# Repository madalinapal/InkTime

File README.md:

# InkTime Smartwatch

## Overview
InkTime Watch is a low-power smartwatch based on the nRF52840 microcontroller, designed for efficient timekeeping, motion tracking, and e-paper display usage.

## Hardware diagram & features

This is an open-hardware wearable based on the nRF52840 microcontroller. It is fully compatible with embedded C/C++ development and comes with the following features:

* [nRF52840](https://files.seeedstudio.com/wiki/XIAO-BLE/Nano_BLE_MCU-nRF52840_PS_v1.1.pdf) microcontroller (ARM Cortex-M4F @ 64 MHz, Bluetooth 5 / BLE, 2.4 GHz radio, 1 MB Flash and 256 KB RAM, multiple interfaces: SPI, I2C, UART, GPIO, support for external antenna)
* [E-paper Display](https://www.waveshare.com/1.54inch-e-paper-module.htm?srsltid=AfmBOooLaZDBFF5ey5FPMcwvfQjNszGLTJooliuUE0Pt89mi3RbbW3zz) 1.54 inch, 200x200 resolution, communicating via SPI interface
* [BMA423](https://watchy.sqfmi.com/assets/files/BST-BMA423-DS000-1509600-950150f51058597a6234dd3eaafbb1f0.pdf) accelerometer (3-axis ultra-low-power MEMS accelerometer, integrated step counting and activity recognition, motion detection interrupts, FIFO buffer, I2C/SPI interface, optimized for wearable low-power applications)
* [BQ25180](https://www.ti.com/product/BQ25180) LiPo Charger (I2C-controlled single-cell Li-Ion/Li-Po charger, 5V USB input, up to ~250 mA charging current, integrated power path management, ultra-low power for wearables)
* [250 mAh LiPo battery](https://elektronik.ropla.eu/pdf/stock/aky/aky1119.pdf)
* [FIT0774](https://www.tme.eu/ro/details/df-fit0774/motoare-dc/dfrobot/fit0774/) vibration motor (small DC vibration motor, 10 mm diameter, 2.7 mm height, 1.5–4.2 V operating voltage, used for haptic feedback in wearable devices)
* [TC2030-IDC](https://www.digikey.ro/ro/products/detail/tag-connect-llc/TC2030-IDC/4571121) debug connector (Tag-Connect 10-pin SWD programming interface, no-socket pogo-pin connector, supports SWDIO, SWDCLK, RESET, VCC and GND, used for low-profile in-circuit debugging of MCUs)
* [DRV2605L](https://www.ti.com/product/DRV2605L) haptic driver (I2C-controlled vibration motor driver with integrated haptic library, supports ERM and LRA actuators, automatic resonance tuning, low-power operation for wearable haptic feedback systems)
* [DS6160A](https://www.mouser.com/datasheet/2/1458/DS6160A_02-3104604.pdf?srsltid=AfmBOorjUBAXZpq5Z5uEI1jLcgjTr8TjWB5ry58Sj_L0fmmZSXPHWXP2) regulator (dual-channel low-power audio power amplifier / driver IC, designed for small speaker or actuator applications, wide supply voltage range, high efficiency Class-D operation, suitable for compact battery-powered systems)
* [MAX17048](https://www.analog.com/en/products/max17048.html) fuel gauge (ultra-low-power single-cell Li-ion battery fuel gauge IC, I2C interface, uses ModelGauge algorithm for accurate state-of-charge estimation, no external sense resistor required, optimized for wearable and portable devices)

## Bill of Materials (BOM)

The table below summarizes the main components used in the project. Passive components are grouped by type and package to improve readability.

| Component | Description | Qty | Manufacturer | Part Number | Datasheet | 
|----------|------------|-----|--------------|-------------|-----------|
| nRF52840 | BLE Microcontroller | 1 | Nordic Semiconductor | nRF52840 | [Datasheet](https://files.seeedstudio.com/wiki/XIAO-BLE/Nano_BLE_MCU-nRF52840_PS_v1.1.pdf) | 
| BMA423 | 3-axis accelerometer (IMU) | 1 | Bosch | BMA423 | [Datasheet](https://watchy.sqfmi.com/assets/files/BST-BMA423-DS000-1509600-950150f51058597a6234dd3eaafbb1f0.pdf) |
| BQ25180 | Battery charger / PMIC | 1 | Texas Instruments | BQ25180 | [Datasheet](https://www.ti.com/product/BQ25180) |
| DRV2605L | Haptic driver | 1 | Texas Instruments | DRV2605L | [Datasheet](https://www.ti.com/product/DRV2605L) |
| MAX17048 | Fuel gauge | 1 | Analog Devices | MAX17048G+T10 | [Datasheet](https://www.analog.com/en/products/max17048.html) | 
| RT6160 | Buck-boost converter | 1 | Richtek | RT6160AWSC | [Datasheet](https://www.mouser.com/datasheet/2/1458/DS6160A_02-3104604.pdf) | 
| 2450AT18B100E | 2.4GHz chip antenna | 1 | Johanson Technology | 2450AT18B100E | [Datasheet](https://jlcpcb.com/api/file/downloadByFileSystemAccessId/8588940948130156544) |
| TC2030-IDC | Programming connector | 1 | Tag-Connect | TC2030-IDC | [Datasheet](https://www.lcsc.com/datasheet/C5444772.pdf) | 
| USB-C Connector | Power & data interface | 1 | Kinghelm | KH-TYPE-C-16P | [Datasheet](https://jlcpcb.com/api/file/downloadByFileSystemAccessId/8588905154556923904) | 
| FPC Connector | E-paper display connector | 1 | Molex | 503480-2400 |[Datasheet](https://www.molex.com/content/dam/molex/molexdotcom/products/automated/enus/salesdrawingpdf/503/503480/5034802400_sd.pdf?inline)| 
| Push Buttons | Tactile switches | 3 | Panasonic | EVP-AKE31A | [Datasheet](https://wmsc.lcsc.com/wmsc/upload/file/pdf/v2/lcsc/2301111010_PANASONIC-EVPAKE31A_C569760.pdf) | 
| MOSFETs | Power switching | 2 | Vishay / Diodes Inc. | SI1308EDL / DMG2305UX | [Datasheet](https://www.lcsc.com/datasheet/C469327.pdf) | 
| Diodes | Schottky diodes | 3 | ON Semiconductor | MBR0530 | [Datasheet](https://www.lcsc.com/datasheet/C77336.pdf) | 
| ESD Protection | USB protection | 1 | STMicroelectronics | USBLC6-2SC6 | [Datasheet](https://www.lcsc.com/datasheet/C7519.pdf) | 
| Crystal | 32MHz | 1 | NDK | NX2016SA-32MHZ-EXS00A-CS11336 | [Datasheet](https://wmsc.lcsc.com/wmsc/upload/file/pdf/v2/lcsc/2312080231_NDK-NX2016SA-32MHZ-EXS00A-CS11336_C6134317.pdf) | 
| Crystals | 32.768kHz | 1 | Seiko Epson | FC-135 32.7680KA-A3 | [Datasheet](https://jlcpcb.com/partdetail/SeikoEpson-FC_135_32_7680KAA3/C2650472) | 

## nRF52840 Pin Mapping

| Pin nRF52840 | Signal      | Component | Interface |
|-------------|------------|------------|----------|
| P0.00/XL1   | XL1        | Crystal X2 (32.768kHz) | XTAL |
| P0.01/XL2   | XL2        | Crystal X2 (32.768kHz) | XTAL |
| P0.05/AIN3  | EPD_CS     | E-Paper (J1 FPC) | SPI CS |
| P0.06       | SDA        | BMA423, BQ25180, MAX17048, DRV2605 | I2C SDA |
| P0.07       | SCL        | BMA423, BQ25180, MAX17048, DRV2605 | I2C SCL |
| P0.08       | IMU_INT1   | BMA423 | GPIO Input |
| P1.08       | IMU_INT2   | BMA423 | GPIO Input |
| P0.11       | PMIC_INT   | BQ25180 | GPIO Input |
| P0.12       | HAPTIC_EN  | DRV2605 | GPIO |
| VBUS        | VBUS       | USB-C (J4) | Power |
| D-          | D-         | USB-C (J4) / USBLC6 | USB |
| D+          | D+         | USB-C (J4) / USBLC6 | USB |
| P0.13       | SW_UP      | Buton Up | GPIO Input |
| P0.14       | SW_ENT     | Buton Enter | GPIO Input |
| P0.15       | EPD_DC     | E-Paper (J1 FPC) | SPI DC |
| P0.16       | EPD_RST    | E-Paper (J1 FPC) | GPIO |
| P0.17       | EPD_BUSY   | E-Paper (J1 FPC) | GPIO Input |
| P0.18/RESET | RESET      | TC2030-IDC | SWD/GPIO |
| SWDCLK      | SWDCLK     | TC2030-IDC | SWD |
| SWDIO       | SWDIO      | TC2030-IDC | SWD |
| P1.02       | SW_DN      | Buton Down | GPIO Input |
| P0.10/NFC2  | ALERT      | MAX17048 | GPIO Input |
| ANT         | RF         | Antena 2450AT18B100E | RF |
| P0.02/AIN0  | SCK        | E-Paper (J1 FPC) | SPI SCK |
| P0.03/AIN1  | MOSI       | E-Paper (J1 FPC) | SPI MOSI |

## Design Log

This section describes the PCB design process, decisions taken during implementation, and how the project complies with the imposed design constraints.

---

###  Placement Strategy

The layout process started with the placement of mechanically constrained and critical components such as:
- USB-C connector
- Side buttons
- E-paper display connector (FPC)
- nRF52840 microcontroller

These components were positioned according to the mechanical enclosure to ensure proper alignment and usability.

All components were placed exclusively on the **TOP layer**, as required. Passive components (resistors, capacitors) were then distributed around their corresponding ICs, minimizing trace length and ensuring proper decoupling.

Special attention was given to **100nF decoupling capacitors**, which were placed as close as possible to the power pins of each integrated circuit.

---

###  Routing Strategy

Routing was performed on a **4-layer PCB stack-up**, structured as follows:
- Top Layer – signal routing and component placement
- Inner Layer 1 – solid ground plane (GND)
- Inner Layer 2 – power plane (VCC, 3V3, etc.)
- Bottom Layer – signal routing

The routing process followed a hierarchical approach:
- Power traces (VCC, VBUS, 3V3) were routed first
- Signal traces were routed afterwards

Design rules applied:
- Power traces: **≥ 0.3 mm width** 
- Signal traces: **≥ 0.15 mm width**
- No 90° angles were used (only smooth or 45° routing)

The use of internal planes significantly improved power distribution and return paths, reducing noise and ensuring signal integrity.

---

###  Grounding and Planes

A solid grounding strategy was implemented using **polygon pours** on ground layers.

- Ground planes were applied on multiple layers
- **Via stitching** was used extensively to connect ground planes
- Increased via density was applied near the RF section

This improves:
- Signal return paths
- Noise reduction
- EMI performance

---

###  RF and Antenna Considerations

The antenna area was treated as a strict keep-out zone:
- No copper
- No traces
- No vias

---

### Component Constraints

All components respect the required footprint rules:

- Resistors: **0201**
- Capacitors ≤100nF: **0201**
- Capacitors >100nF: **0402**
  
## Design Rule Exceptions (Accepted)

**Trace Width (accepted):**  
Power nets (3V3, VREG, VBAT, VBUS) follow the 0.3 mm rule, but in dense areas around the nRF52840 and tightly packed components, traces are locally reduced due to limited space. These segments are short and were accepted after verification.

**Copper Clearance (accepted):**  
The minimum clearance rule (0.15 mm) is slightly violated in congested regions, especially near the nRF52840 and 0201 components. All cases were manually checked to ensure no shorts.

**Board Edge Clearance (accepted):**  
The USB-C connector (J4) and buttons (SW_UP, SW_DN, SW_ENT) extend beyond the PCB edge for enclosure alignment. This is intentional.

This ensures high-density integration suit

## Repository contens
- schematic.sch → Schematic design file  
- board.brd → PCB layout file  

### Manufacturing
- GerberFiles.zip → PCB manufacturing files (Gerber + drill files)  
- bom.csv / bom.xlsx → Bill of Materials  
- pick&place.cpl → Component placement file 

### Mechanical
- smartwatch_exploded_view.stp → Full 3D exploded view (PCB + battery + display + enclosure)  
- smartwatch.stp → Full 3D view 

### Images
- pcb_2d.png 
- pcb_3d_top_view.png
- pcb_3d_bottom_view.png
- pcb_3d_side_view
- block_diagram.jpg
- smartwatch_final.png
- smartwatch_side_view1.png
- smartwatch_side_view2.png
- smartwatch_exploded_view.png

### License
- LICENSE → Open-source license file 

### Documentation
- README.md → Main project documentation

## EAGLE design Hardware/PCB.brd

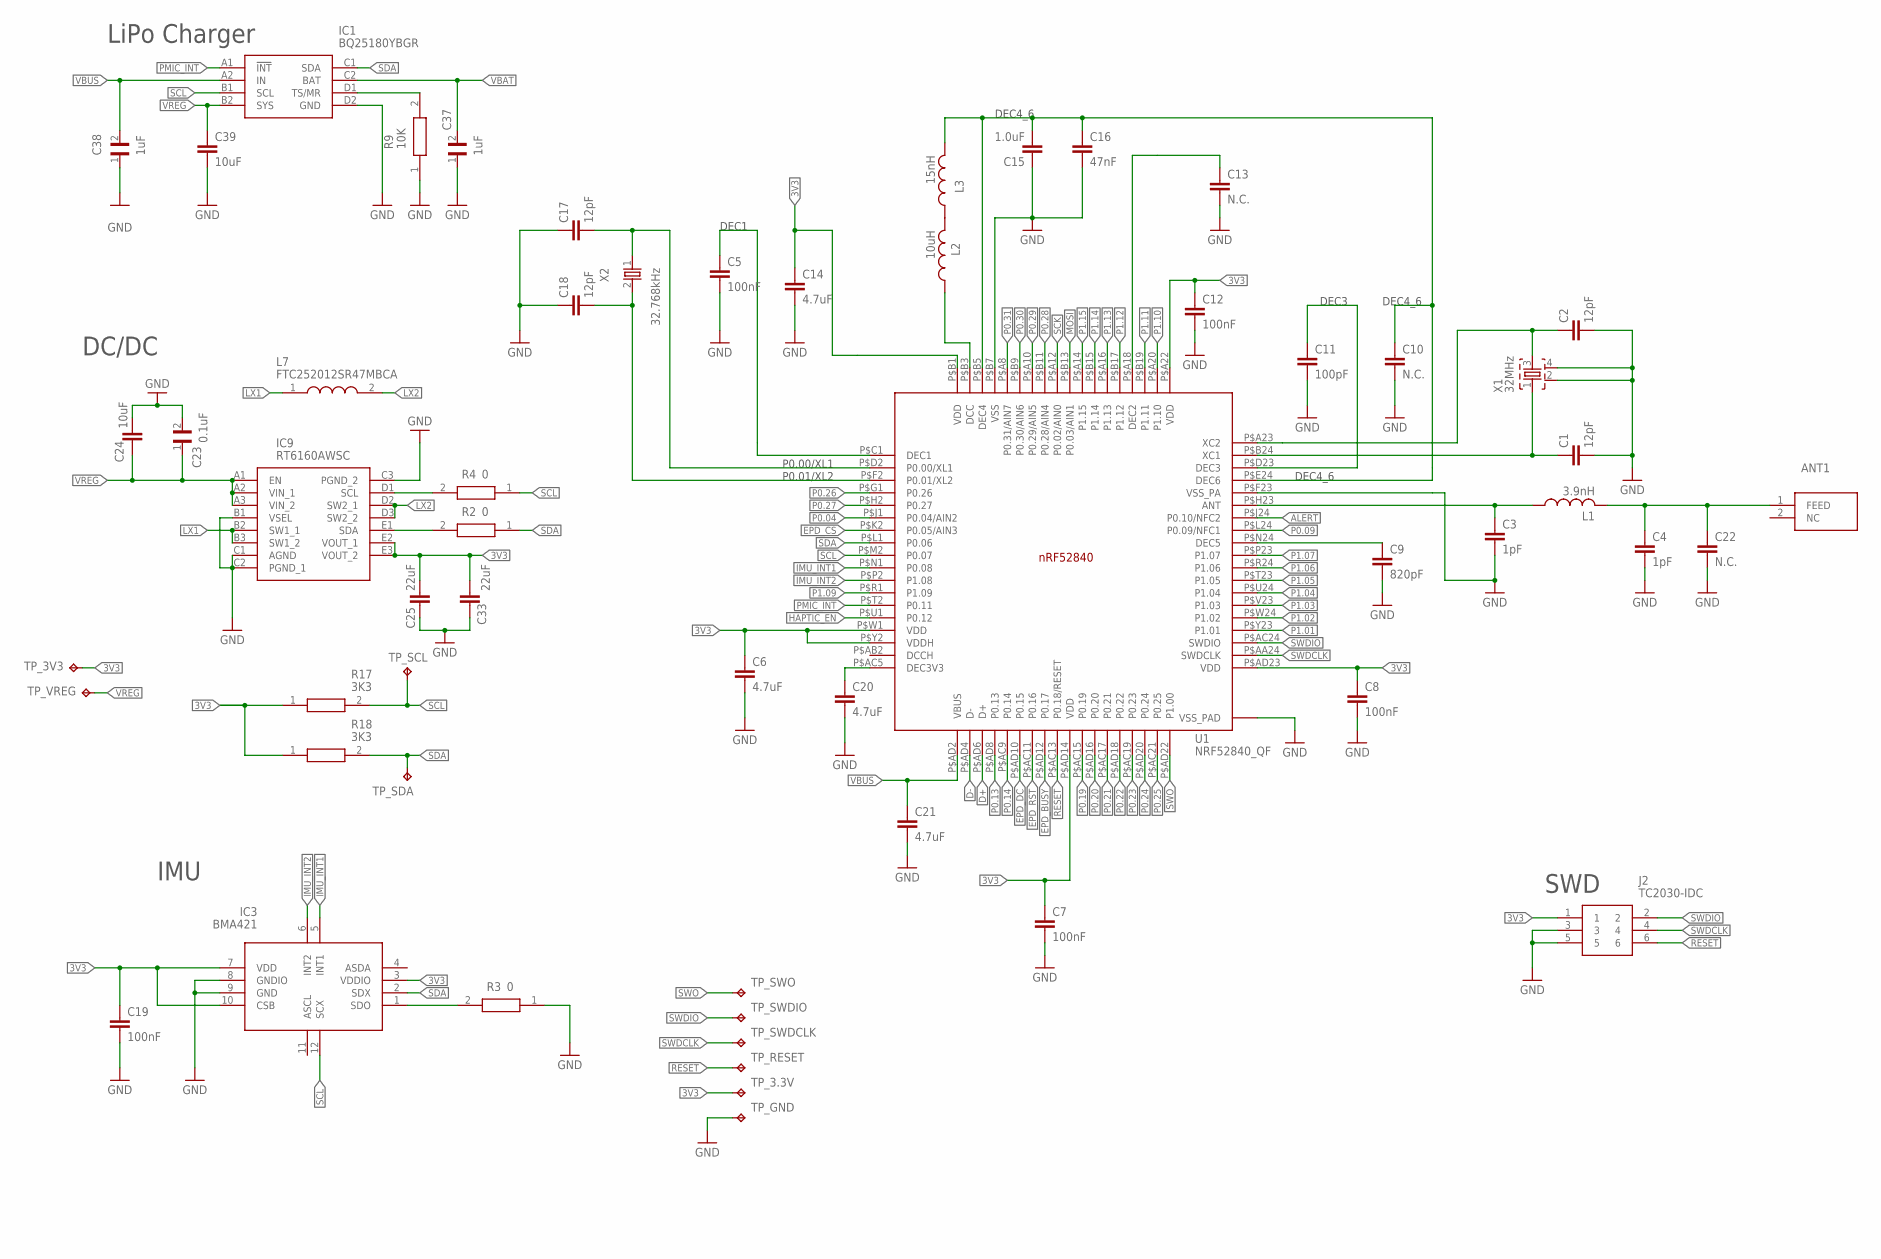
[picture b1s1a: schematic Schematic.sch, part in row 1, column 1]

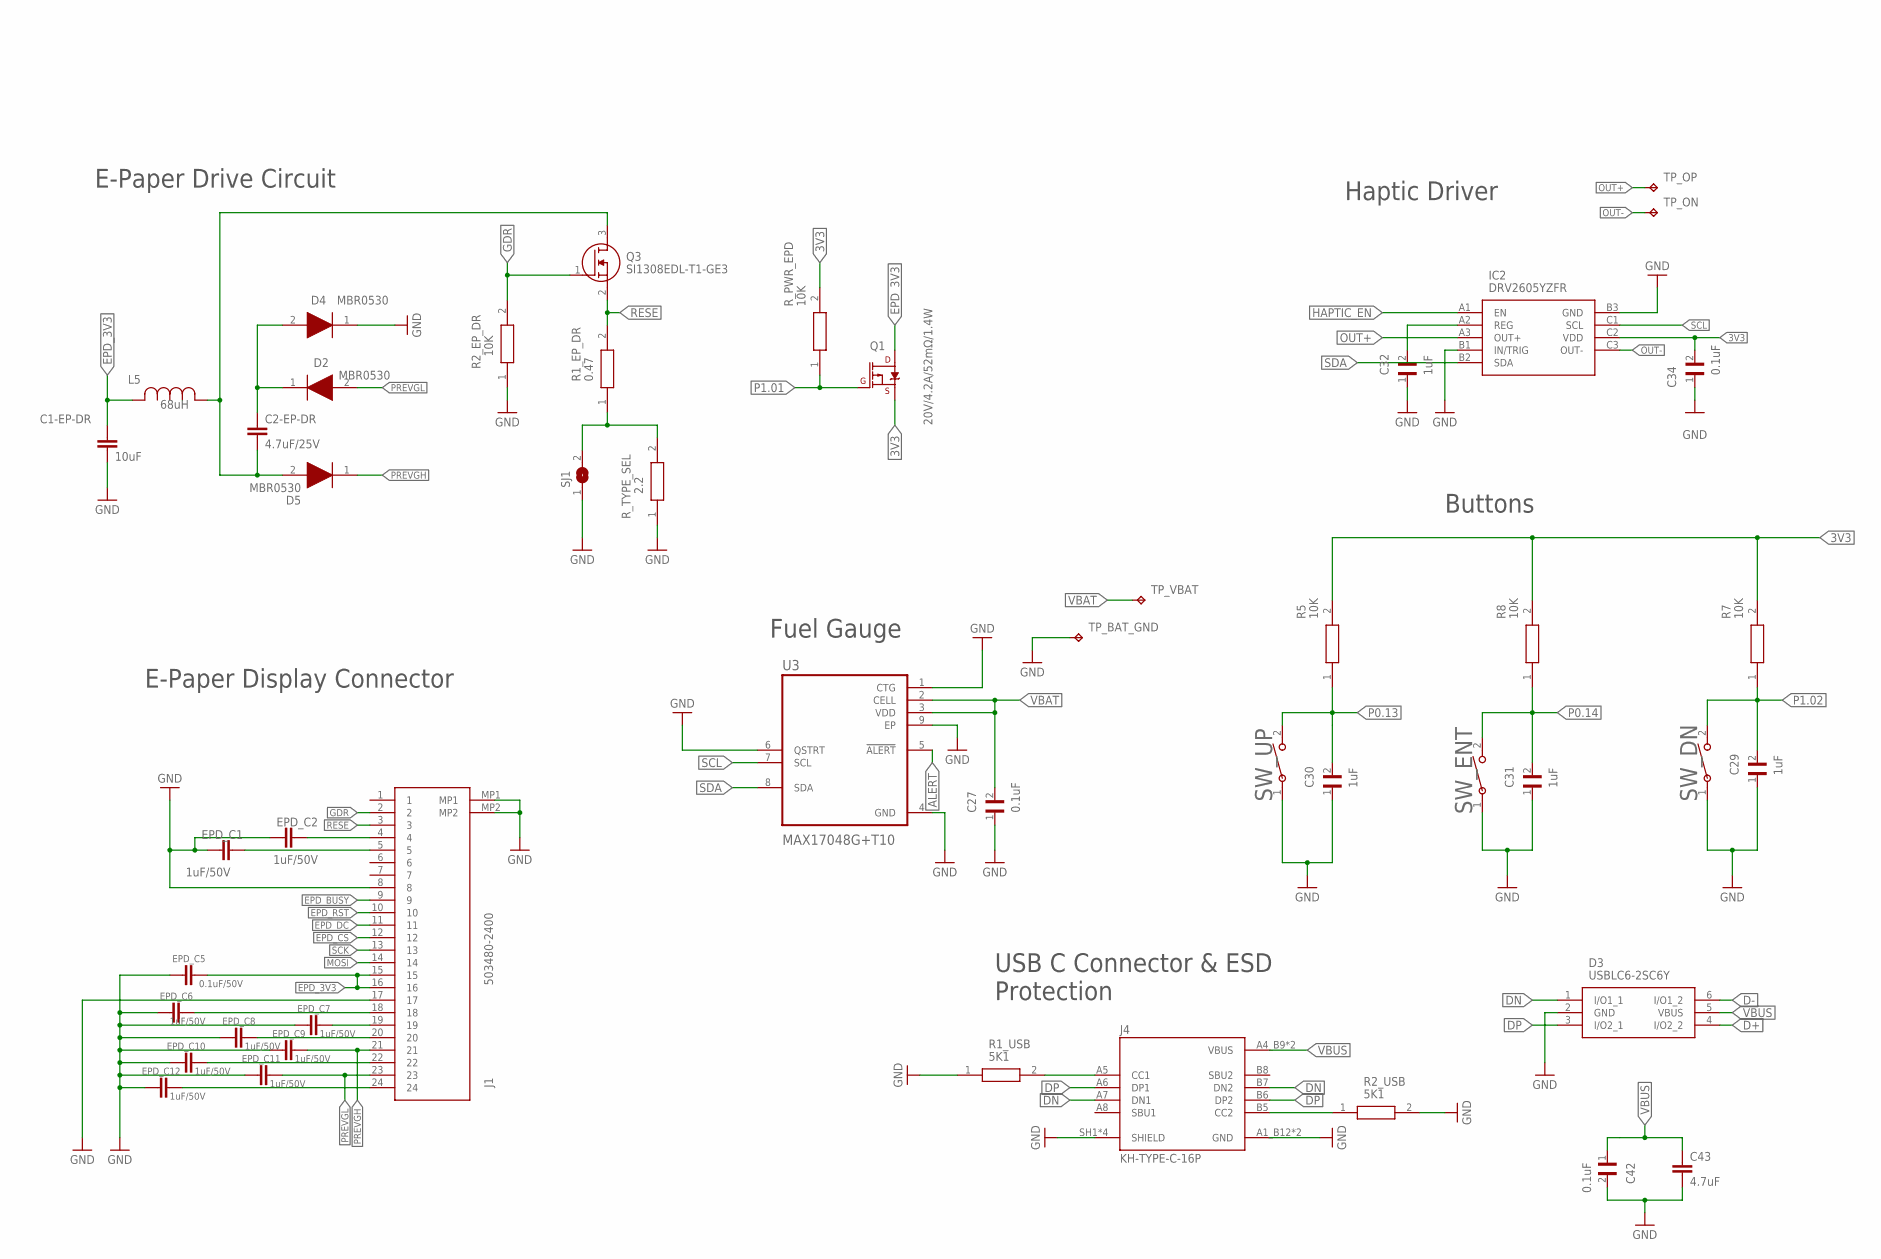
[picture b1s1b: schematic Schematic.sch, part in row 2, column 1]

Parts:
ANT1: 2450AT18B100E_2450AT18B100E; 2450AT18B100E_ANTC3216X140N
C1, C2, C17, C18: 12pF; PERFECT_0402_0402
C1-EP-DR, C24, C39: 10uF; PERFECT_0402_0402
C2-EP-DR: 4.7uF/25V; PERFECT_0402_0402
C3, C4: 1pF; PERFECT_0402_0402
C5, C7, C8, C12, C19: 100nF; PERFECT_0402_0402
C6, C14, C20, C21, C43: 4.7uF; PERFECT_0402_0402
C9: 820pF; PERFECT_0402_0402
C10, C13, C22: N.C.; PERFECT_0402_0402
C11: 100pF; PERFECT_0402_0402
C15: 1.0uF; PERFECT_0402_0402
C16: 47nF; PERFECT_0402_0402
C23, C27: 0.1uF; GRM011R60J152KE01L_1_0201
C25, C33: 22uF; PERFECT_0402_0402
C29, C30, C31, C37, C38: 1uF; GRM011R60J152KE01L_1_0201
C32: 1uF; GRM011R60J152KE01L_2_CAPC0201X13N
C34, C42: 0.1uF; GRM011R60J152KE01L_2_CAPC0201X13N
D2, D4, D5: MBR0530; ESP32_C6_LIBRARY_5_SOD3716X135N
D3: USBLC6-2SC6Y; ESP32_C6_LIBRARY_3_SOT95P280X145-6N
EPD_C1, EPD_C2, EPD_C6, EPD_C7, EPD_C8, EPD_C9, EPD_C10, EPD_C11, EPD_C12: 1uF/50V; NORDIC_NRF_3_RESC0201_L
EPD_C5: 0.1uF/50V; NORDIC_NRF_3_RESC0201_L
IC1: BQ25180YBGR; BQ25180YBGR_BGA8C40P2X4_100X155X50
IC2: DRV2605YZFR; DRV2605YZFR_BGA9C50P3X3_144X144X62
IC3: BMA421; BMA423_BMA423
IC9: RT6160AWSC; RT6160AWSC_BGA15C40P3X5_140X230X60
J1: 503480-2400; 503480-2400_5034802400
J2: TC2030-IDC; TC2030-IDC_TC2030IDC
J4: KH-TYPE-C-16P; KH-TYPE-C-16P_KINGHELM_KH-TYPE-C-16P
L1: 3.9nH; NORDIC_NRF_2_RESC0402_L
L2: 10uH; NORDIC_NRF_2_RESC0402_L
L3: 15nH; NORDIC_NRF_2_RESC0402_L
L5: 68uH; ESP32_C6_LIBRARY_2_IND_4828-WE-TPC_WRE
L7: FTC252012SR47MBCA; MLP2016SR47MT0S1_INDC2016X100N
Q1: 20V/4.2A/52mΩ/1.4W; ESP32_C6_LIBRARY_4_ESP32_C6_LIBRARY_4_ESP32_C6_LIBRARY_4_ES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
Q3: SI1308EDL-T1-GE3; ESP32_C6_LIBRARY_6_SOT65P210X110-3N
R1_EP_DR: 0.47; CPF0201D7K68C1_0201
R1_USB, R2_USB: 5K1; CPF0201D7K68C1_0201
R2, R3, R4: 0; ERA-1AEB3401C_0201
R2_EP_DR, R9: 10K; CPF0201D7K68C1_0201
R5, R7, R8: 10K; ERA-1AEB3401C_0201
R17, R18: 3K3; ERA-1AEB3401C_0201
R_PWR_EPD: 10K; ERA-1AEB3401C_0201
R_TYPE_SEL: 2.2; CPF0201D7K68C1_0201
SJ1: ESP32_C6_LIBRARY_7_JUMPER_SJ
SW_DN: 2025-10-22_07-23-44_LIBRARY_EVP-AKE31ASW_EVP-AKE3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; 2025-10-22_07-23-44_LIBRARY_SW_EVP-AKE31A_PAN
SW_ENT: 2025-10-22_07-23-44_LIBRARY_EVP-AKE31ASW_EVP-AKE3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; 2025-10-22_07-23-44_LIBRARY_SW_EVP-AKE31A_PAN
SW_UP: 2025-10-22_07-23-44_LIBRARY_EVP-AKE31ASW_EVP-AKE3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; 2025-10-22_07-23-44_LIBRARY_SW_EVP-AKE31A_PAN
TP_3.3V, TP_3V3: HECTOR_WATCH_1_TPTP20R; HECTOR_WATCH_1_TP20R
TP_BAT_GND: HECTOR_WATCH_1_TPTP20R; HECTOR_WATCH_1_TP20R
TP_GND: HECTOR_WATCH_1_TPTP20R; HECTOR_WATCH_1_TP20R
TP_ON: HECTOR_WATCH_1_TPTP20R; HECTOR_WATCH_1_TP20R
TP_OP: HECTOR_WATCH_1_TPTP20R; HECTOR_WATCH_1_TP20R
TP_RESET: HECTOR_WATCH_1_TPTP20R; HECTOR_WATCH_1_TP20R
TP_SCL: HECTOR_WATCH_1_TPTP20R; HECTOR_WATCH_1_TP20R
TP_SDA: HECTOR_WATCH_1_TPTP20R; HECTOR_WATCH_1_TP20R
TP_SWDCLK: HECTOR_WATCH_1_TPTP20R; HECTOR_WATCH_1_TP20R
TP_SWDIO: HECTOR_WATCH_1_TPTP20R; HECTOR_WATCH_1_TP20R
TP_SWO: HECTOR_WATCH_1_TPTP20R; HECTOR_WATCH_1_TP20R
TP_VBAT: HECTOR_WATCH_1_TPTP20R; HECTOR_WATCH_1_TP20R
TP_VREG: HECTOR_WATCH_1_TPTP20R; HECTOR_WATCH_1_TP20R
U1: NRF52840_QF; NORDIC_NRF_4_AQFN50P700X700X85_HS-74N
U3: MAX17048G+T10; ESP32_C6_LIBRARY_SON50P200X200X80-9N
X1: 32MHz; NORDIC_NRF_BT-XTAL_2016_N
X2: 32.768kHz; NORDIC_NRF_1_XTAL_3215_N

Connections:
3V3: C6.1, C7.1, C8.1, C12.1, C14.1, C19.1, C25.1, C33.1, C34.2, IC2.C2 (VDD), IC3.3 (VDDIO), IC3.7 (VDD), IC3.10 (CSB), IC9.E2 (VOUT_1), IC9.E3 (VOUT_2), J2.1, Q1.2 (S), R5.2, R7.2, R8.2, R17.1, R18.1, R_PWR_EPD.2, TP_3.3V.TP, TP_3V3.TP, U1.P$A22 (VDD), U1.P$AD14 (VDD), U1.P$AD23 (VDD), U1.P$B1 (VDD), U1.P$W1 (VDD), U1.P$Y2 (VDDH)
ALERT: U1.P$J24 (P0.10/NFC2), U3.5 (!ALERT)
D+: D3.4 (I/O2_2), U1.P$AD6 (D+)
D-: D3.6 (I/O1_2), U1.P$AD4 (D-)
DN: D3.1 (I/O1_1), J4.A7 (DN1), J4.B7 (DN2)
DP: D3.3 (I/O2_1), J4.A6 (DP1), J4.B6 (DP2)
EPD_3V3: C1-EP-DR.1, EPD_C5.2, J1.15, J1.16, L5.2, Q1.3 (D)
EPD_BUSY: J1.9, U1.P$AD12 (P0.17)
EPD_CS: J1.12, U1.P$K2 (P0.05/AIN3)
EPD_DC: J1.11, U1.P$AD10 (P0.15)
EPD_RST: J1.10, U1.P$AC11 (P0.16)
GDR: J1.2, Q3.1 (G), R2_EP_DR.2
GND: C1.2, C1-EP-DR.2, C2.2, C3.2, C4.2, C5.2, C6.2, C7.2, C8.2, C9.2, C10.2, C11.2, C12.2, C13.2, C14.2, C15.1, C16.2, C17.1, C18.1, C19.2, C20.2, C21.2, C22.2, C23.2, C24.1, C25.2, C27.1, C29.1, C30.1, C31.1, C32.1, C33.2, C34.1, C37.1, C38.1, C39.2, C42.2, C43.2, D3.2 (GND), D4.1 (K), EPD_C1.1, EPD_C2.1, EPD_C5.1, EPD_C6.1, EPD_C7.1, EPD_C8.1, EPD_C9.1, EPD_C10.1, EPD_C11.1, EPD_C12.1, IC1.D2 (GND), IC2.B1 (IN/TRIG), IC2.B3 (GND), IC3.8 (GNDIO), IC3.9 (GND), IC9.B1 (VSEL), IC9.C1 (AGND), IC9.C2 (PGND_1), IC9.C3 (PGND_2), J1.8, J1.17, J1.MP1, J1.MP2, J2.3, J2.5, J4.A1_B12 (GND), J4.A12_B1 (GND), J4.SH1 (SHIELD), J4.SH2 (SHIELD), J4.SH3 (SHIELD), J4.SH4 (SHIELD), R1_USB.1, R2_EP_DR.1, R2_USB.2, R3.1, R9.1, R_TYPE_SEL.1, SJ1.1, SW_DN.1, SW_ENT.1, SW_UP.1, TP_BAT_GND.TP, TP_GND.TP, U1.P$74 (VSS_PAD), U1.P$75 (VSS_PAD), U1.P$76 (VSS_PAD), U1.P$77 (VSS_PAD), U1.P$78 (VSS_PAD), U1.P$79 (VSS_PAD), U1.P$80 (VSS_PAD), U1.P$81 (VSS_PAD), U1.P$82 (VSS_PAD), U1.P$83 (VSS_PAD), U1.P$84 (VSS_PAD), U1.P$85 (VSS_PAD), U1.P$86 (VSS_PAD), U1.P$87 (VSS_PAD), U1.P$88 (VSS_PAD), U1.P$89 (VSS_PAD), U1.P$90 (VSS_PAD), U1.P$B7 (VSS), U1.P$F23 (VSS_PA), U3.1 (CTG), U3.4 (GND), U3.6 (QSTRT), U3.9 (EP), X1.2, X1.4
HAPTIC_EN: IC2.A1 (EN), U1.P$U1 (P0.12)
IMU_INT1: IC3.5 (INT1), U1.P$N1 (P0.08)
IMU_INT2: IC3.6 (INT2), U1.P$P2 (P1.08)
LX1: IC9.B2 (SW1_1), IC9.B3 (SW1_2), L7.1
LX2: IC9.D2 (SW2_1), IC9.D3 (SW2_2), L7.2
MOSI: J1.14, U1.P$B13 (P0.03/AIN1)
unnamed: IC1.D1 (TS/MR), R9.2
unnamed: IC9.D1 (SCL), R4.2
unnamed: IC9.E1 (SDA), R2.2
unnamed: IC3.1 (SDO), R3.2
unnamed: C20.1, U1.P$AC5 (DEC3V3)
unnamed: C9.1, U1.P$N24 (DEC5)
unnamed: ANT1.1 (FEED), C4.1, C22.1, L1.2
unnamed: C3.1, L1.1, U1.P$H23 (ANT)
unnamed: C2.1, U1.P$A23 (XC2), X1.3
unnamed: C1.1, U1.P$B24 (XC1), X1.1
unnamed: C5.1, U1.P$C1 (DEC1)
unnamed: C18.2, U1.P$F2 (P0.01/XL2), X2.2
unnamed: C17.2, U1.P$D2 (P0.00/XL1), X2.1
unnamed: C11.1, U1.P$D23 (DEC3)
unnamed: C2-EP-DR.2, D5.2 (A), L5.1, Q3.3 (D)
unnamed: C13.1, U1.P$A18 (DEC2)
unnamed: L2.2, L3.1
unnamed: L2.1, U1.P$B3 (DCC)
unnamed: C10.1, C15.2, C16.1, L3.2, U1.P$B5 (DEC4), U1.P$E24 (DEC6)
unnamed: C2-EP-DR.1, D2.1 (K), D4.2 (A)
unnamed: EPD_C2.2, J1.4
unnamed: R1_EP_DR.1, R_TYPE_SEL.2, SJ1.2
unnamed: EPD_C1.2, J1.5
unnamed: C32.2, IC2.A2 (REG)
unnamed: EPD_C6.2, J1.18
unnamed: EPD_C7.2, J1.19
unnamed: J4.A5 (CC1), R1_USB.2
unnamed: J4.B5 (CC2), R2_USB.1
unnamed: EPD_C8.2, J1.20
unnamed: EPD_C10.2, J1.22
unnamed: EPD_C12.2, J1.24
OUT+: IC2.A3 (OUT+), TP_OP.TP
OUT-: IC2.C3 (OUT-), TP_ON.TP
P0.04: U1.P$J1 (P0.04/AIN2)
P0.09: U1.P$L24 (P0.09/NFC1)
P0.13: C30.2, R5.1, SW_UP.2, U1.P$AD8 (P0.13)
P0.14: C31.2, R8.1, SW_ENT.2, U1.P$AC9 (P0.14)
P0.19: U1.P$AC15 (P0.19)
P0.20: U1.P$AD16 (P0.20)
P0.21: U1.P$AC17 (P0.21)
P0.22: U1.P$AD18 (P0.22)
P0.23: U1.P$AC19 (P0.23)
P0.24: U1.P$AD20 (P0.24)
P0.25: U1.P$AC21 (P0.25)
P0.26: U1.P$G1 (P0.26)
P0.27: U1.P$H2 (P0.27)
P0.28: U1.P$B11 (P0.28/AIN4)
P0.29: U1.P$A10 (P0.29/AIN5)
P0.30: U1.P$B9 (P0.30/AIN6)
P0.31: U1.P$A8 (P0.31/AIN7)
P1.01: Q1.1 (G), R_PWR_EPD.1, U1.P$Y23 (P1.01)
P1.02: C29.2, R7.1, SW_DN.2, U1.P$W24 (P1.02)
P1.03: U1.P$V23 (P1.03)
P1.04: U1.P$U24 (P1.04)
P1.05: U1.P$T23 (P1.05)
P1.06: U1.P$R24 (P1.06)
P1.07: U1.P$P23 (P1.07)
P1.09: U1.P$R1 (P1.09)
P1.10: U1.P$A20 (P1.10)
P1.11: U1.P$B19 (P1.11)
P1.12: U1.P$B17 (P1.12)
P1.13: U1.P$A16 (P1.13)
P1.14: U1.P$B15 (P1.14)
P1.15: U1.P$A14 (P1.15)
PMIC_INT: IC1.A1 (!INT), U1.P$T2 (P0.11)
PREVGH: D5.1 (K), EPD_C9.2, J1.21
PREVGL: D2.2 (A), EPD_C11.2, J1.23
RESE: J1.3, Q3.2 (S), R1_EP_DR.2
RESET: J2.6, TP_RESET.TP, U1.P$AC13 (P0.18/RESET)
SCK: J1.13, U1.P$A12 (P0.02/AIN0)
SCL: IC1.B1 (SCL), IC2.C1 (SCL), IC3.12 (SCX), R4.1, R17.2, TP_SCL.TP, U1.P$M2 (P0.07), U3.7 (SCL)
SDA: IC1.C1 (SDA), IC2.B2 (SDA), IC3.2 (SDX), R2.1, R18.2, TP_SDA.TP, U1.P$L1 (P0.06), U3.8 (SDA)
SWDCLK: J2.4, TP_SWDCLK.TP, U1.P$AA24 (SWDCLK)
SWDIO: J2.2, TP_SWDIO.TP, U1.P$AC24 (SWDIO)
SWO: TP_SWO.TP, U1.P$AD22 (P1.00)
VBAT: C27.2, C37.2, IC1.C2 (BAT), TP_VBAT.TP, U3.2 (CELL), U3.3 (VDD)
VBUS: C21.1, C38.2, C42.1, C43.1, D3.5 (VBUS), IC1.A2 (IN), J4.A4_B9 (VBUS), J4.A9_B4 (VBUS), U1.P$AD2 (VBUS)
VREG: C23.1, C24.2, C39.1, IC1.B2 (SYS), IC9.A1 (EN), IC9.A2 (VIN_1), IC9.A3 (VIN_2), TP_VREG.TP

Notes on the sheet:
LiPo Charger
DC/DC
IMU
DEC4_6
DEC3
DEC1
P0.00/XL1
P0.01/XL2
SWD
E-Paper Drive Circuit
Haptic Driver
Buttons
Fuel Gauge
USB C Connector & ESD Protection
E-Paper Display Connector

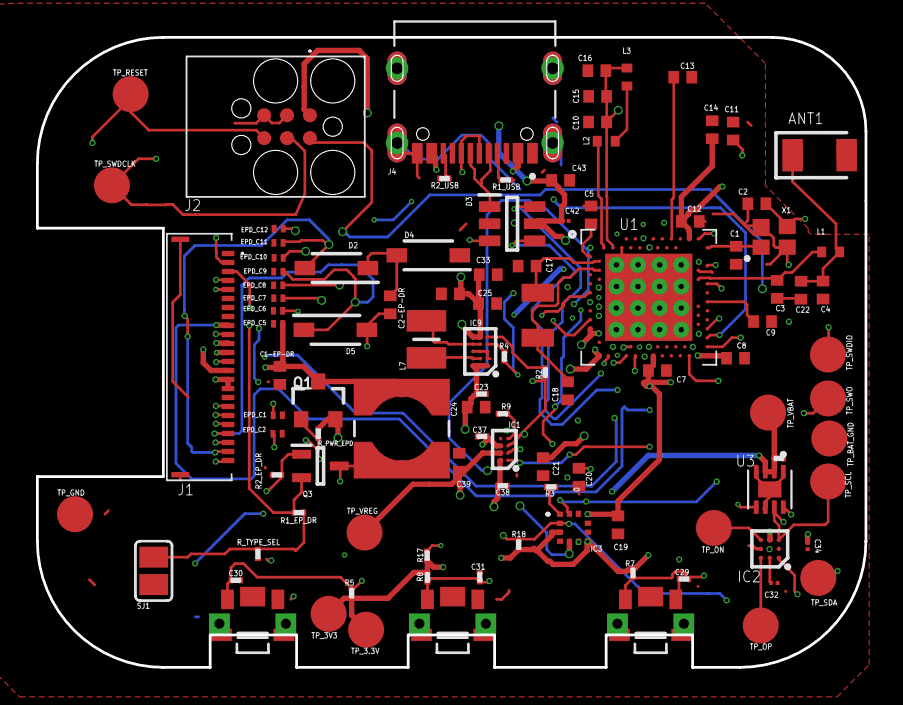
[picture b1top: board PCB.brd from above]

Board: 2 copper layers, 46.0 x 35.0 mm, 105 parts (0 on the bottom side), 70 nets.

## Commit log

2026-04-09 uploaded files
2026-04-09 Add GPL v3 license file
    Added the GNU General Public License version 3 to the project.
2026-04-09 Initialize README with project details
    Add project overview and hardware diagram to README
2026-04-09 Update README with hardware features and specifications
    Added detailed hardware features and specifications for the InkTime Watch.
2026-04-09 Update README with nRF52840 pin mapping and contents
    Added detailed pin mapping for nRF52840 and repository contents.
2026-04-09 Add Design Log section to README
    Added a section for the design log in the README.
2026-04-10 Fix BOM table formatting and update links
2026-04-10 updated pcb
2026-04-10 Update README with design rule exceptions
    Added design rule exceptions for trace width, copper clearance, and board edge clearance.
2026-04-10 updated 1 photo
2026-04-19 Solved .DS_Store problem
2026-04-19 Remove all DS_Store files
2026-04-19 solved issue

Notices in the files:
parts and their libraries:
COPYRIGHT: Copyright (C) 2024 Ultra Librarian. All rights reserved.
COPYRIGHT: Copyright (C) 2025 Ultra Librarian. All rights reserved.
